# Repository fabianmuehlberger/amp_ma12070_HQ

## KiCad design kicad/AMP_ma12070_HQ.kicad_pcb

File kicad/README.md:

# AUDIO AMP ma12070/p

PCB for ma12070p Merus IC ref design

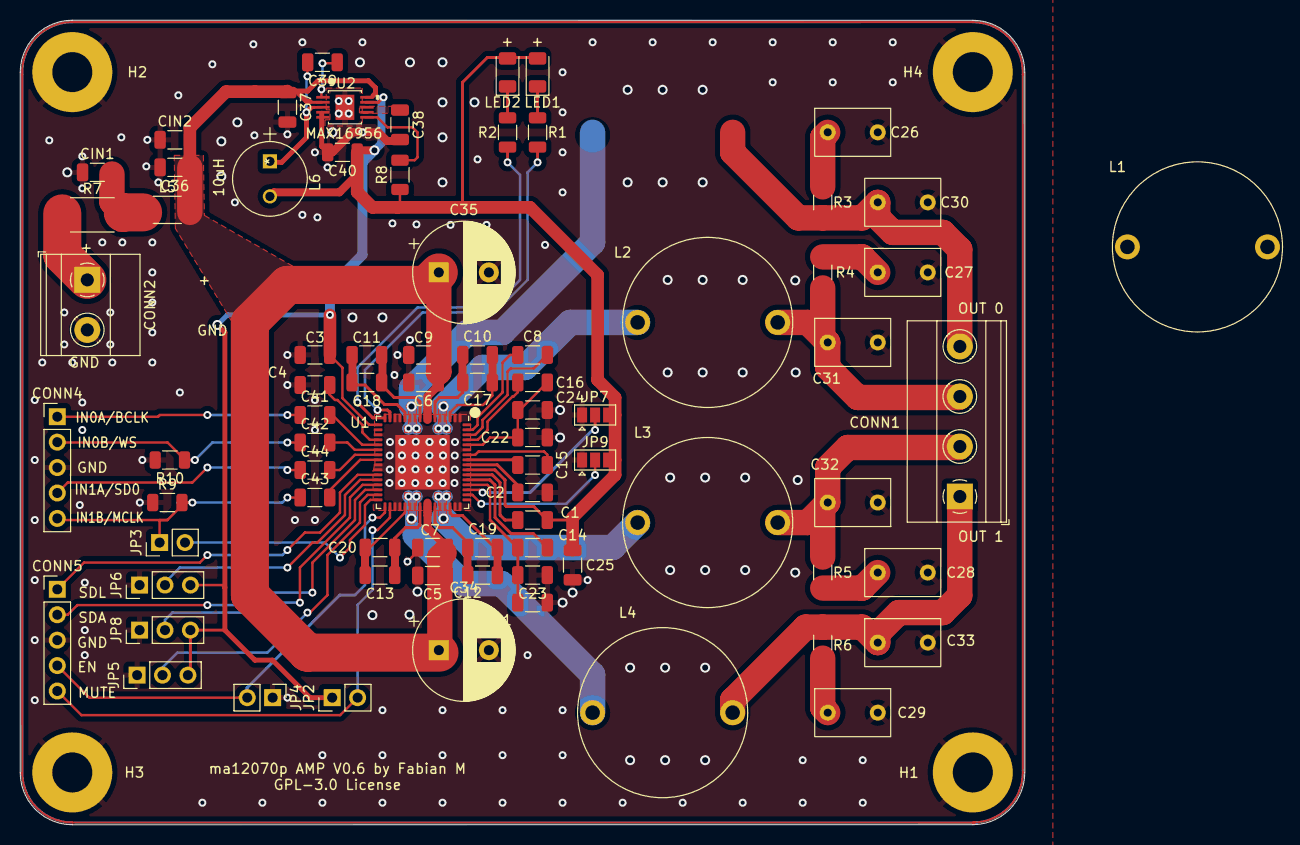
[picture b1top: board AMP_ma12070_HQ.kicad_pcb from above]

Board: 2 copper layers, 100.4 x 80.4 mm, 82 parts (0 on the bottom side), 58 nets.

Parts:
C1, C2, C3, C4, C5, C9, C14, C15, C16, C21, C22, C25, C38, C41, C42, C43, C44: 1uF; C_1206_3216Metric
C6, C7, C8, C23, C24, C37, C39: 0.1uF; C_1206_3216Metric
C10, C11, C12, C13, C17, C18, C19, C20, C36: 10uF; C_1206_3216Metric
C26, C27, C28, C29: 1uF; C_Rect_L7.3_W4.5_P5.0
C30, C31, C32, C33: 0.47uF; C_Rect_L7.3_W4.5_P5.0
C34, C35: 100uF; CP_Radial_D10.0mm_P5.00mm
C40: 22uF; C_1206_3216Metric
CIN1, CIN2: 0.022uF; C_1206_3216Metric
CONN1: Screw_Terminal_01x04; TerminalBlock_Phoenix_MKDS-1,5-4_1x04_P5.00mm_Horizontal
CONN2: Screw_Terminal_01x02; TerminalBlock_Phoenix_MKDS-1,5-2_1x02_P5.00mm_Horizontal
CONN4, CONN5: Conn_01x05; PinHeader_1x05_P2.54mm_Vertical
H1, H2, H3, H4: MountingHole_Pad; MountingHole_4mm_Pad
JP2, JP3, JP4: SolderJumper_2_Open; PinHeader_1x02_P2.54mm_Vertical
JP5, JP8: Jumper:Jumper_3_Open; PinHeader_1x03_P2.54mm_Vertical
JP6: SolderJumper_3_Open; PinHeader_1x03_P2.54mm_Vertical
JP7, JP9: SolderJumper_3_Open; SolderJumper-3_P1.3mm_Open_Pad1.0x1.5mm
L1, L2, L3, L4: 6.8uH; L_Radial_TH_Murata_D16.9_P14.0
L5: 47; L_2010_5025Metric
L6: 10uH; RLB0712-100KL
LED1, LED2: LED; LED_1206_3216Metric
R1, R2: 2k; R_1206_3216Metric
R3, R4, R5, R6: 3.6; R_1206_3216Metric
R7: 0.1R; R_2512_6332Metric
R8: 4.7k; R_1206_3216Metric
R9, R10: 10K; R_1206_3216Metric
U1: MA12070P; QFN-64-1EP_9x9mm_P0.5mm_EP5.45x5.45mm
U2: MAX16956; MAX16956AUBD&slash_V&plus_

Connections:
/CDC: C2.1, U1.56 (CDC)
/CF0AN: C10.2, C17.2, U1.3 (CF0AN)
/CF0AP: C10.1, C17.1, U1.6 (CF0AP)
/CF0BN: C11.2, C18.2, U1.12 (CF0BN)
/CF0BP: C11.1, C18.1, U1.9 (CF0BP)
/CF1AN: C12.2, C19.2, U1.46 (CF1AN)
/CF1AP: C12.1, C19.1, U1.43 (CF1AP)
/CF1BN: C13.2, C20.2, U1.37 (CF1BN)
/CF1BP: C13.1, C20.1, U1.40 (CF1BP)
/CFD0P: C16.1, C22.1, C24.2, U1.60 (CGD0P)
/CFDCN: C15.2, U1.58 (CFDCN)
/CFDCP: C15.1, U1.57 (CFDCP)
/CFGDN: C8.1, U1.63 (CFGDN)
/CFGDP: C8.2, U1.62 (CFGDP)
/CGD1N: C14.1, C21.1, C23.2, U1.52 (CGD1N)
/CGD1P: C14.2, U1.53 (CGD1P)
/CGDON: C16.2, U1.61 (CGD0N)
/CREF: C4.1, U1.20 (CREF)
/VGDC: C1.2, U1.54 (VGDC)
/power/BIAS/MODE: C38.1, U2.7 (MODE), U2.8 (BIAS)
/power/BST: C39.1, U2.1 (BST)
/power/LX: C39.2, L6.1, U2.3 (LX)
/power/NRST: R8.2, U2.6 (*RESET)
/power/RCSUP: CIN1.2, L5.1, R7.2
/power/VSUP: CONN2.1, R7.1
AD0: JP6.2 (C), U1.28 (AD0)
AD1: JP8.2 (C), U1.29 (AD1)
CLKIO: JP3.2 (B), U1.32 (CLK)
CLKMS: JP5.2 (C), U1.31 (CLKM/S)
ENABLE: CONN5.4, JP4.2 (B), U1.33 (~ENABLE)
GND: C2.2, C3.2, C4.2, C5.2, C6.2, C7.2, C9.2, C21.2, C22.2, C23.1, C24.1, C25.2, C26.2, C27.2, C28.2, C29.2, C30.1, C31.2, C32.1, C33.2, C34.2, C35.2, C36.2, C37.2, C38.2, C40.2, CIN1.1, CIN2.1, CONN2.2, CONN4.3, CONN5.3, H1.1, H2.1, H3.1, H4.1, JP4.1 (A), JP5.1 (A), JP6.1 (A), JP7.1 (A), JP8.1 (A), JP9.1 (A), R9.1, R10.2, U1.1 (PVSS), U1.2 (PVSS), U1.13 (PVSS), U1.14 (PVSS), U1.19 (AVSS), U1.25 (AVSS), U1.26 (DVSS), U1.35 (PVSS), U1.36 (PVSS), U1.47 (PVSS), U1.48 (PVSS), U1.59 (DVSS), U1.65 (PAD), U2.4 (PGND), U2.5 (AGND), U2.EPAD (EP)
IN0A: C41.1, C41.2, CONN4.1, U1.21 (SCLK)
IN0B: C42.1, C42.2, CONN4.2, R10.1, U1.22 (WS)
IN1A: C44.1, C44.2, CONN4.4, U1.23 (SD0)
IN1B: C43.1, C43.2, CONN4.5, JP3.1 (A), R9.2, U1.24 (SD1)
MSEL0: JP7.2 (C), U1.51 (MSEL0)
MSEL1: JP9.2 (C), U1.50 (MSEL1)
MUTE: CONN5.5, JP2.2 (B), U1.34 (~MUTE)
unnamed: C26.1, R3.2
unnamed: C27.1, R4.1
unnamed: C28.1, R5.2
unnamed: C29.1, R6.1
unnamed: C30.2, CONN1.4, L1.1, R3.1
unnamed: C31.1, CONN1.3, L2.1, R4.2
unnamed: C32.2, CONN1.2, L3.1, R5.1
unnamed: C33.1, CONN1.1, L4.1, R6.2
unnamed: LED1.1 (K), R1.2
unnamed: LED2.1 (K), R2.2
unnamed: R1.1, U1.15 (~CLIP)
unnamed: R2.1, U1.16 (~ERROR)
OUT0A: L2.2, U1.4 (OUT0A), U1.5 (OUT0A)
OUT0B: L1.2, U1.10 (OUT0B), U1.11 (OUT0B)
OUT1A: L3.2, U1.44 (OUT1A), U1.45 (OUT1A)
OUT1B: L4.2, U1.38 (OUT1B), U1.39 (OUT1B)
PVDD: C5.1, C6.1, C7.1, C9.1, C34.1, C35.1, C36.1, C37.1, CIN2.2, L5.2, U1.7 (PVDD), U1.8 (PVDD), U1.41 (PVDD), U1.42 (PVDD), U2.2 (SUP), U2.10 (EN)
SDA: CONN5.2, U1.30 (SDA)
SDL: CONN5.1, U1.27 (SCL)
VDD: C1.1, C3.1, C25.1, C40.1, JP2.1 (A), JP5.3 (B), JP6.3 (B), JP7.3 (B), JP8.3 (B), JP9.3 (B), L6.2, LED1.2 (A), LED2.2 (A), R8.1, U1.17 (AVDD), U1.55 (DVDD), U2.9 (OUT)

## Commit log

2022-08-09 changed schematic layout
2022-08-09 minor changes
2022-08-12 ongoing work
2022-08-14 generated pdf schematic
2022-08-16 no changes

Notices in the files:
kicad/AMP_ma12070_HQ.kicad_pcb:
GPL-3.0 License
parts and their libraries:
Copyright 2021 Accelerated Designs. All rights reserved.
